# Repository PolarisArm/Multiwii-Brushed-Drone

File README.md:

# Multiwii-Brushed-Drone
Brushed Drone with Multiwii

# Orientation Code need to be changed as per MPU6050 Placement

# Vibration Issue mitigated by using low pass filter

# Dead band Added

# Multiwii 2.4 Software picture

#Transmitter Schematic

# Transmitter

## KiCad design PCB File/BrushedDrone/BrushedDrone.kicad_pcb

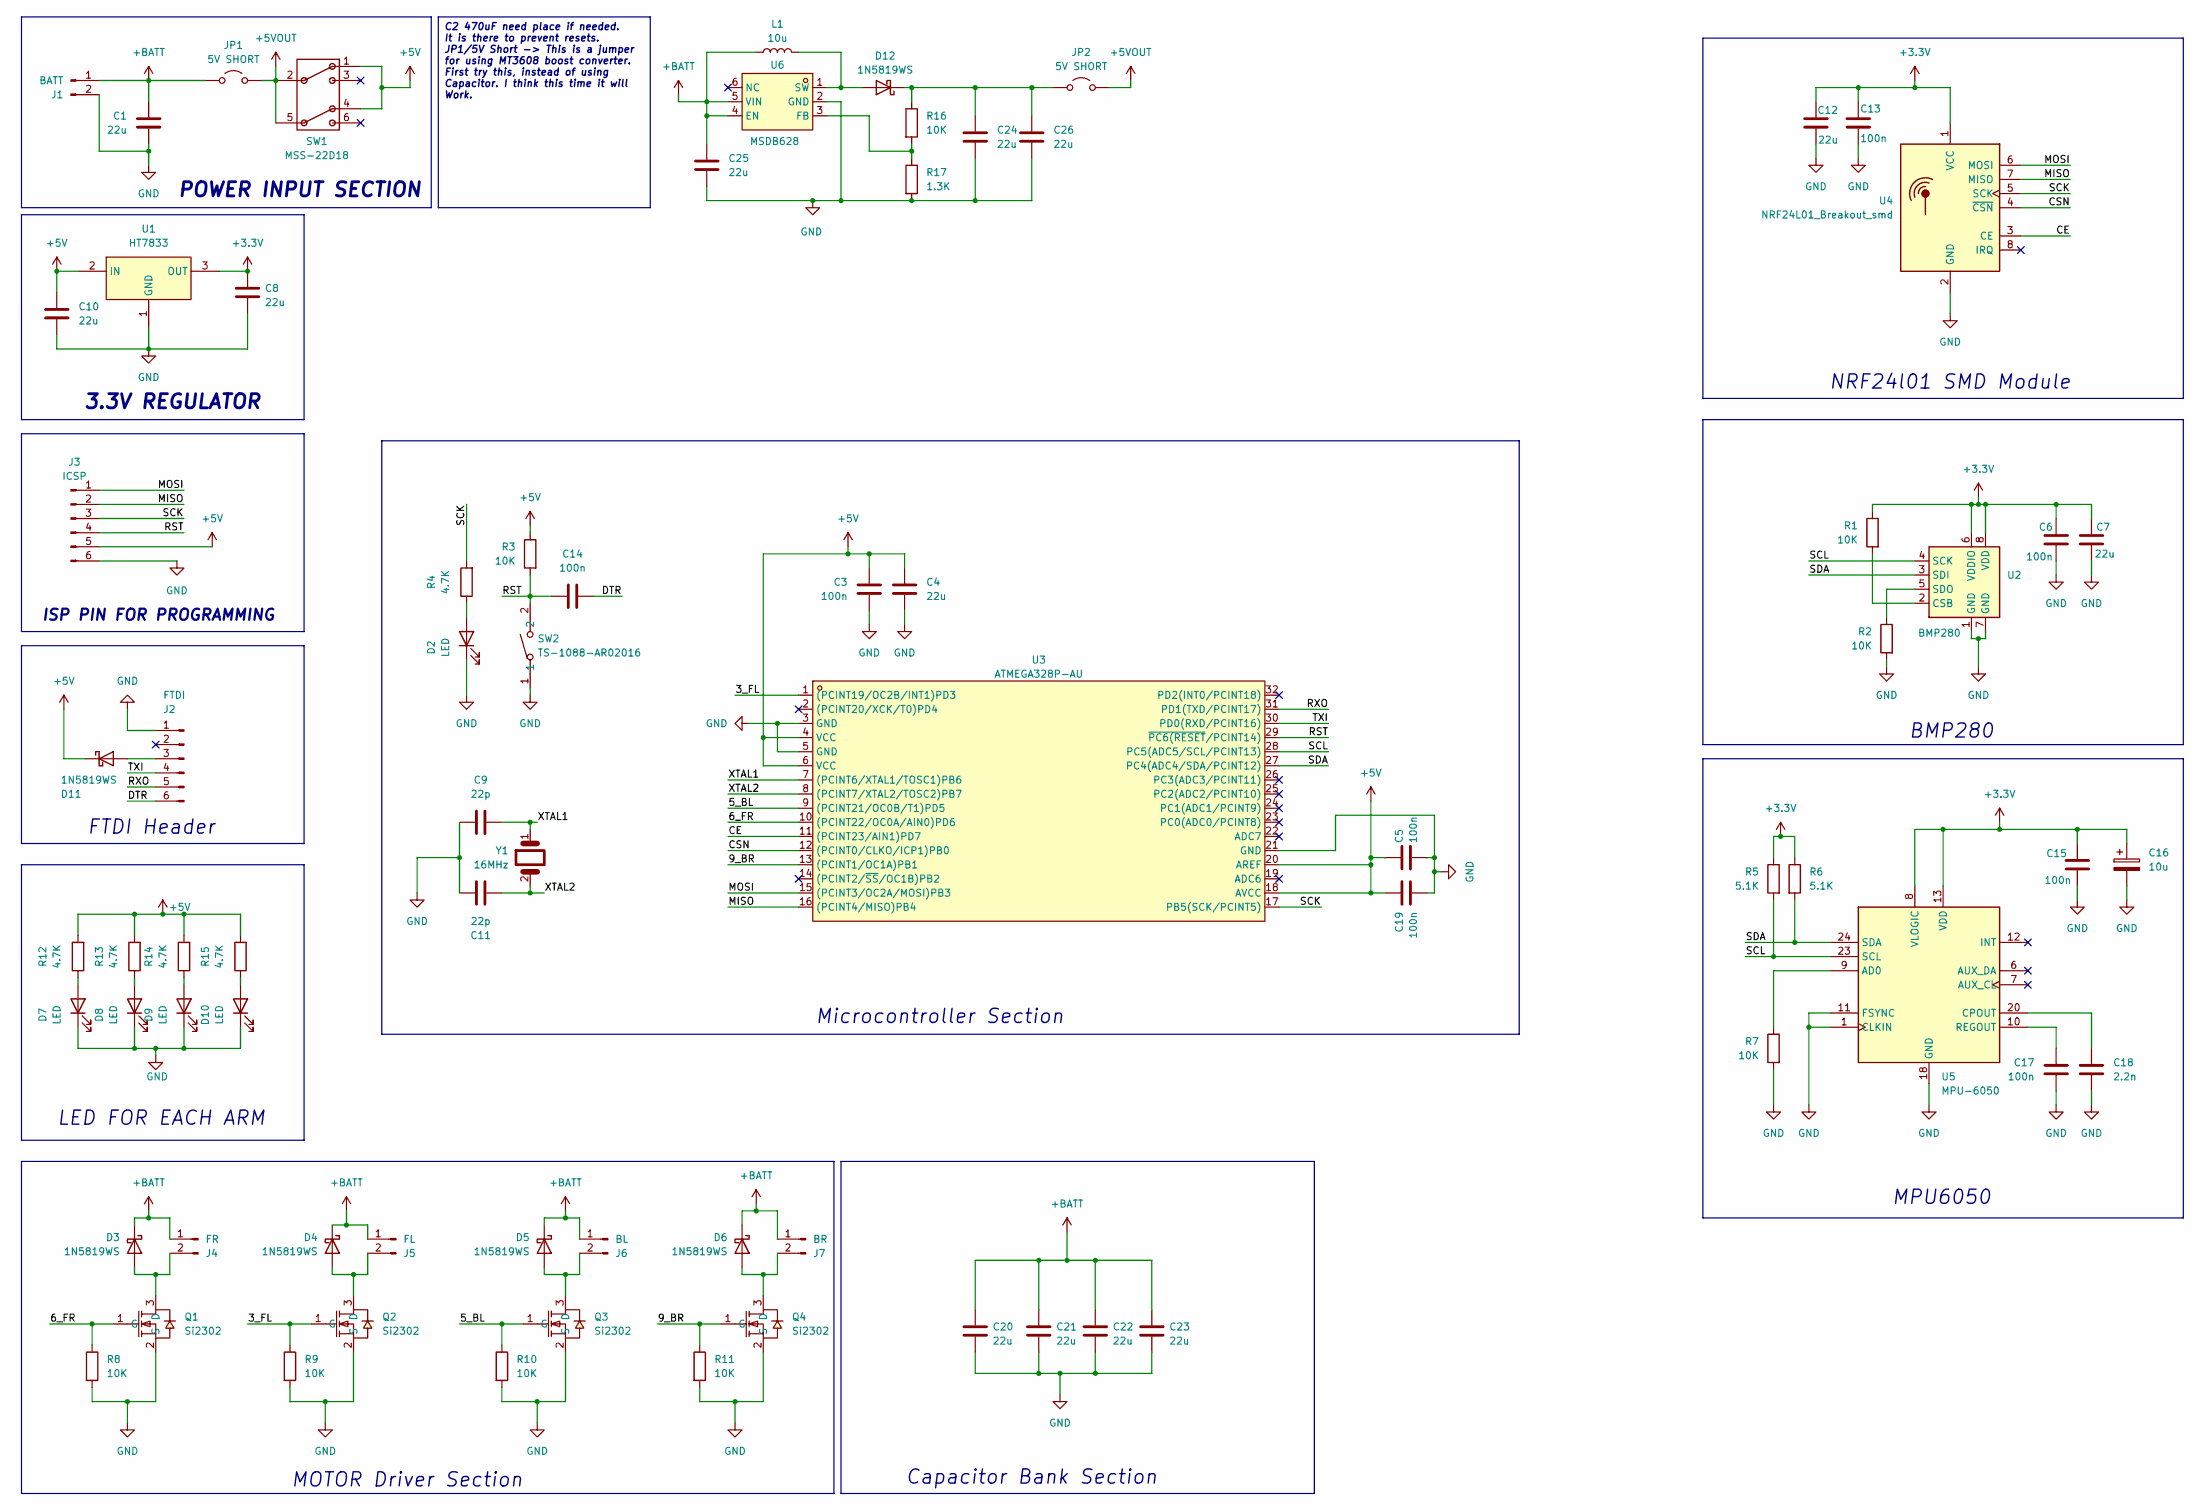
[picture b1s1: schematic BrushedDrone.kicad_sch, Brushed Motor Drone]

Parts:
C1, C4, C7, C8, C10, C12, C20, C21, C22, C23, C24, C25, C26: 22u; C_0805_2012Metric_Pad1.18x1.45mm_HandSolder
C3, C5, C6, C13, C14, C15, C17, C19: 100n; C_0805_2012Metric_Pad1.18x1.45mm_HandSolder
C9, C11: 22p; C_1206_3216Metric_Pad1.33x1.80mm_HandSolder
C16: 10u; CP_EIA-3528-12_Kemet-T_HandSolder
C18: 2.2n; C_0805_2012Metric_Pad1.18x1.45mm_HandSolder
D2, D7, D8, D9, D10: LED; LED_0805_2012Metric_Pad1.15x1.40mm_HandSolder
D3, D4, D5, D6, D11, D12: 1N5819WS; D_SOD-323_HandSoldering
J1: BATT; PinSocket_1x02_P2.54mm_Vertical
J2: FTDI; PinSocket_1x06_P2.54mm_Vertical
J3: ICSP; ICSP_PAD
J4: FR; PinSocket_1x02_P2.54mm_Vertical
J5: FL; PinSocket_1x02_P2.54mm_Vertical
J6: BL; PinSocket_1x02_P2.54mm_Vertical
J7: BR; PinSocket_1x02_P2.54mm_Vertical
JP1: 5V SHORT; TestPoint_2Pads_Pitch2.54mm_Drill0.8mm
JP2: 5V SHORT; SolderJumper-2_P1.3mm_Open_Pad1.0x1.5mm
L1: 10u; L_APV_ANR4020
Q1, Q2, Q3, Q4: Si2302; SOT-23_L2.9-W1.3-P1.90-LS2.4-BR; MPN Si2302CDS-T1-GE3; LCSC Part C10488
R1, R2, R3, R7, R8, R9, R10, R11: 10K; R_0805_2012Metric_Pad1.20x1.40mm_HandSolder
R4, R12, R13, R14, R15: 4.7K; R_0805_2012Metric_Pad1.20x1.40mm_HandSolder
R5, R6: 5.1K; R_0805_2012Metric_Pad1.20x1.40mm_HandSolder
R16: 10K; R_0603_1608Metric_Pad0.98x0.95mm_HandSolder
R17: 1.3K; R_0603_1608Metric_Pad0.98x0.95mm_HandSolder
SW1: MSS-22D18; MSS2D18
SW2: TS-1088-AR02016; SW-SMD_L3.9-W3.0-P4.45; MPN TS-1088-AR02016; LCSC Part C720477
U1: HT7833; SOT-89_L4.5-W2.5-P1.50-LS4.2-BR; MPN HT7833; LCSC Part C50936
U2: BMP280; Bosch_LGA-8_2x2.5mm_P0.65mm_ClockwisePinNumbering
U3: ATMEGA328P-AU; TQFP-32_L7.0-W7.0-P0.80-LS9.0-BL; MPN ATMEGA328P-AU; LCSC Part C14877
U4: NRF24L01_Breakout_smd; FootprintsKeyplus_nordic.prettyNRF24L01-Module-SMD
U5: MPU-6050; InvenSense_QFN-24_4x4mm_P0.5mm
U6: MSDB628; SOT-23-6_L2.9-W1.6-P0.95-LS2.8-BR; MPN MSDB628; LCSC Part C30197563
Y1: 16MHz; Crystal_HC49-4H_Vertical

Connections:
+3.3V: C6.1, C7.1, C8.1, C12.1, C13.1, C15.1, C16.1, R1.1, R5.1, R6.1, U1.3 (OUT), U2.6 (VDDIO), U2.8 (VDD), U4.1 (VCC), U5.8 (VLOGIC), U5.13 (VDD)
+5V: C3.1, C4.1, C5.1, C10.1, C19.1, D11.1 (K), J3.5, R3.1, R12.2, R13.2, R14.2, R15.2, SW1.1, SW1.4, U1.2 (IN), U3.4 (VCC), U3.6 (VCC), U3.18 (AVCC), U3.20 (AREF)
+5VOUT: JP1.2 (B), JP2.2 (B), SW1.2, SW1.5
+BATT: C1.1, C20.1, C21.1, C22.1, C23.1, C25.1, D3.1 (K), D4.1 (K), D5.1 (K), D6.1 (K), J1.1, J4.1, J5.1, J6.1, J7.1, JP1.1 (A), L1.1, U6.4 (EN), U6.5 (VIN)
/3_FL: Q2.1 (G), R9.1, U3.1 ((PCINT19/OC2B/INT1)PD3)
/5_BL: Q3.1 (G), R10.1, U3.9 ((PCINT21/OC0B/T1)PD5)
/6_FR: Q1.1 (G), R8.1, U3.10 ((PCINT22/OC0A/AIN0)PD6)
/9_BR: Q4.1 (G), R11.1, U3.13 ((PCINT1/OC1A)PB1)
/CE: U3.11 ((PCINT23/AIN1)PD7), U4.3 (CE)
/CSN: U3.12 ((PCINT0/CLKO/ICP1)PB0), U4.4 (~CSN)
/DTR: C14.2, J2.6
/MISO: J3.2, U3.16 ((PCINT4/MISO)PB4), U4.7 (MISO)
/MOSI: J3.1, U3.15 ((PCINT3/OC2A/MOSI)PB3), U4.6 (MOSI)
/RST: C14.1, J3.4, R3.2, SW2.2, U3.29 (~PC6(RESET/PCINT14))
/RXO: J2.5, U3.31 (PD1(TXD/PCINT17))
/SCK: J3.3, R4.2, U3.17 (PB5(SCK/PCINT5)), U4.5 (SCK)
/SCL: R5.2, U2.4 (SCK), U3.28 (PC5(ADC5/SCL/PCINT13)), U5.23 (SCL)
/SDA: R6.2, U2.3 (SDI), U3.27 (PC4(ADC4/SDA/PCINT12)), U5.24 (SDA)
/TXI: J2.4, U3.30 (PD0(RXD/PCINT16))
/XTAL1: C9.1, U3.7 ((PCINT6/XTAL1/TOSC1)PB6), Y1.1
/XTAL2: C11.1, U3.8 ((PCINT7/XTAL2/TOSC2)PB7), Y1.2
GND: C1.2, C3.2, C4.2, C5.2, C6.2, C7.2, C8.2, C9.2, C10.2, C11.2, C12.2, C13.2, C15.2, C16.2, C17.2, C18.2, C19.2, C20.2, C21.2, C22.2, C23.2, C24.2, C25.2, C26.2, D2.1 (K), D7.1 (K), D8.1 (K), D9.1 (K), D10.1 (K), J1.2, J2.1, J3.6, Q1.2 (S), Q2.2 (S), Q3.2 (S), Q4.2 (S), R2.2, R7.2, R8.2, R9.2, R10.2, R11.2, R17.2, SW2.1, U1.1 (GND), U2.1 (GND), U2.7 (GND), U3.3 (GND), U3.5 (GND), U3.21 (GND), U4.2 (GND), U5.1 (CLKIN), U5.11 (FSYNC), U5.18 (GND), U6.2 (GND)
unnamed: D2.2 (A), R4.1
unnamed: D3.2 (A), J4.2, Q1.3 (D)
unnamed: D4.2 (A), J5.2, Q2.3 (D)
unnamed: D5.2 (A), J6.2, Q3.3 (D)
unnamed: D6.2 (A), J7.2, Q4.3 (D)
unnamed: D7.2 (A), R12.1
unnamed: D8.2 (A), R13.1
unnamed: D9.2 (A), R14.1
unnamed: D10.2 (A), R15.1
unnamed: D11.2 (A), J2.3
unnamed: D12.2 (A), L1.2, U6.1 (SW)
unnamed: C24.1, C26.1, D12.1 (K), JP2.1 (A), R16.1
unnamed: R1.2, U2.2 (CSB)
unnamed: R2.1, U2.5 (SDO)
unnamed: R7.1, U5.9 (AD0)
unnamed: C18.1, U5.20 (CPOUT)
unnamed: C17.1, U5.10 (REGOUT)
unnamed: R16.2, R17.1, U6.3 (FB)

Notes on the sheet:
NRF24l01 SMD Module
BMP280
ISP PIN FOR PROGRAMMING
MOTOR Driver Section
MPU6050
LED FOR EACH ARM
POWER INPUT SECTION
Microcontroller Section
3.3V REGULATOR
Capacitor Bank Section
FTDI Header
C2 470uF need place if needed. It is there to prevent resets. JP1/5V Short -> This is a jumper for using MT3608 boost converter. First try this, instead of using Capacitor. I think this time it will Work.

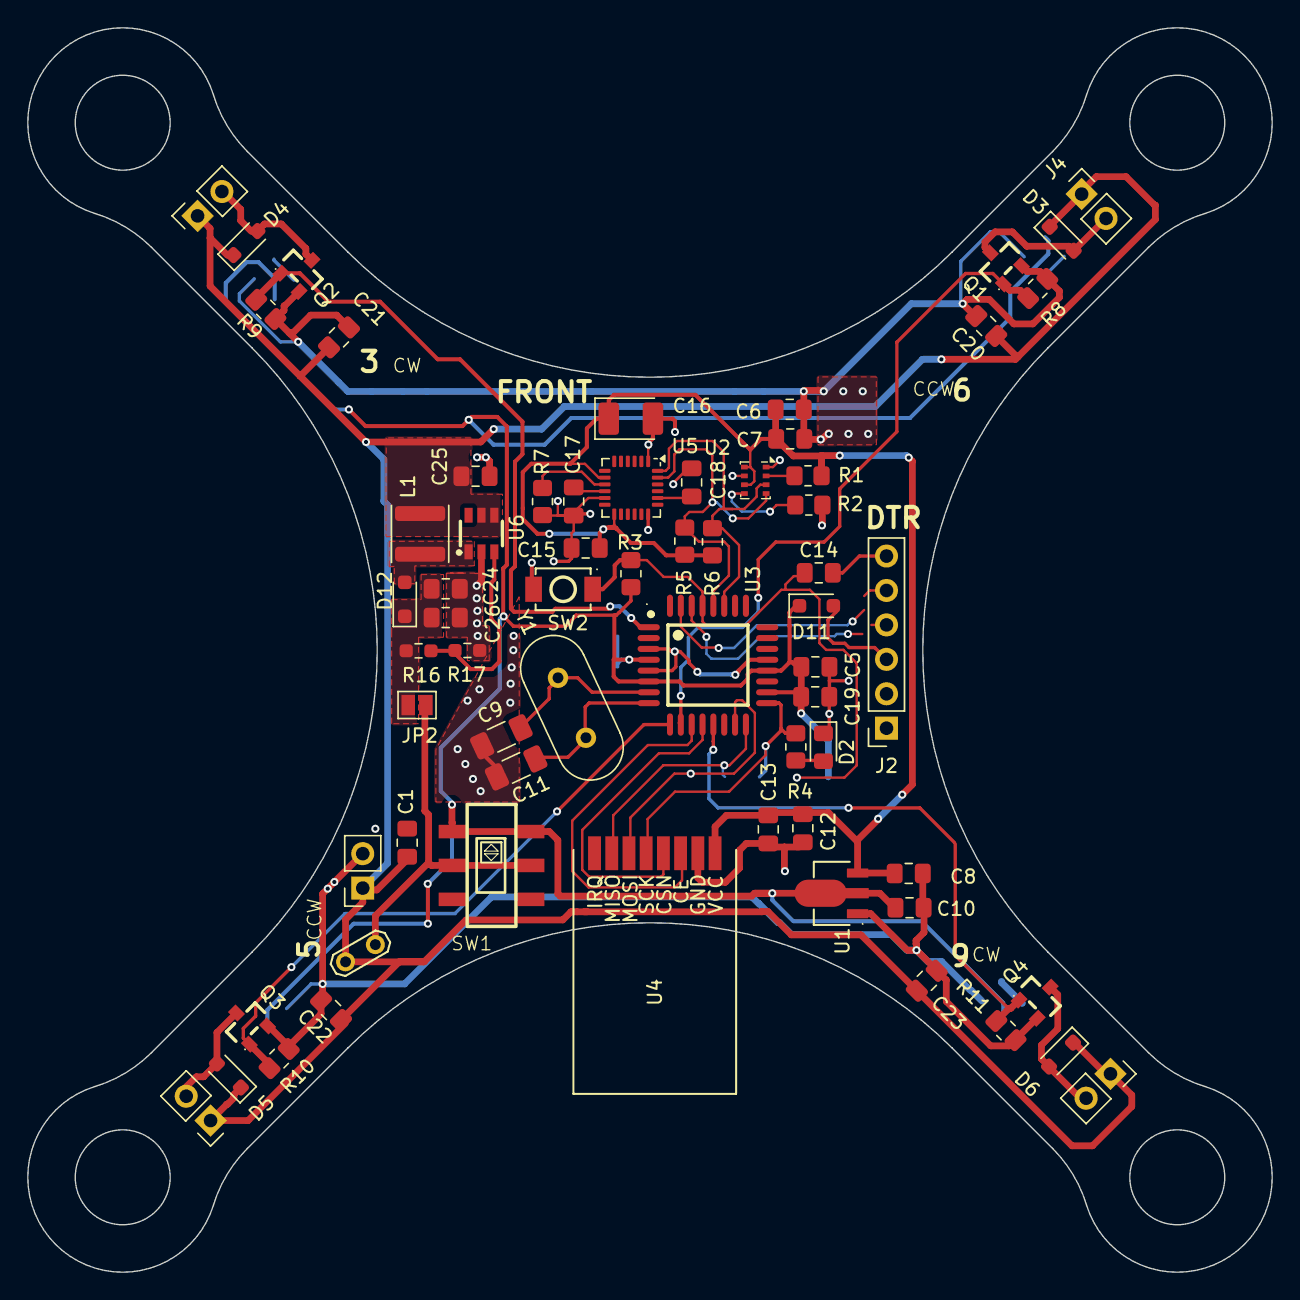
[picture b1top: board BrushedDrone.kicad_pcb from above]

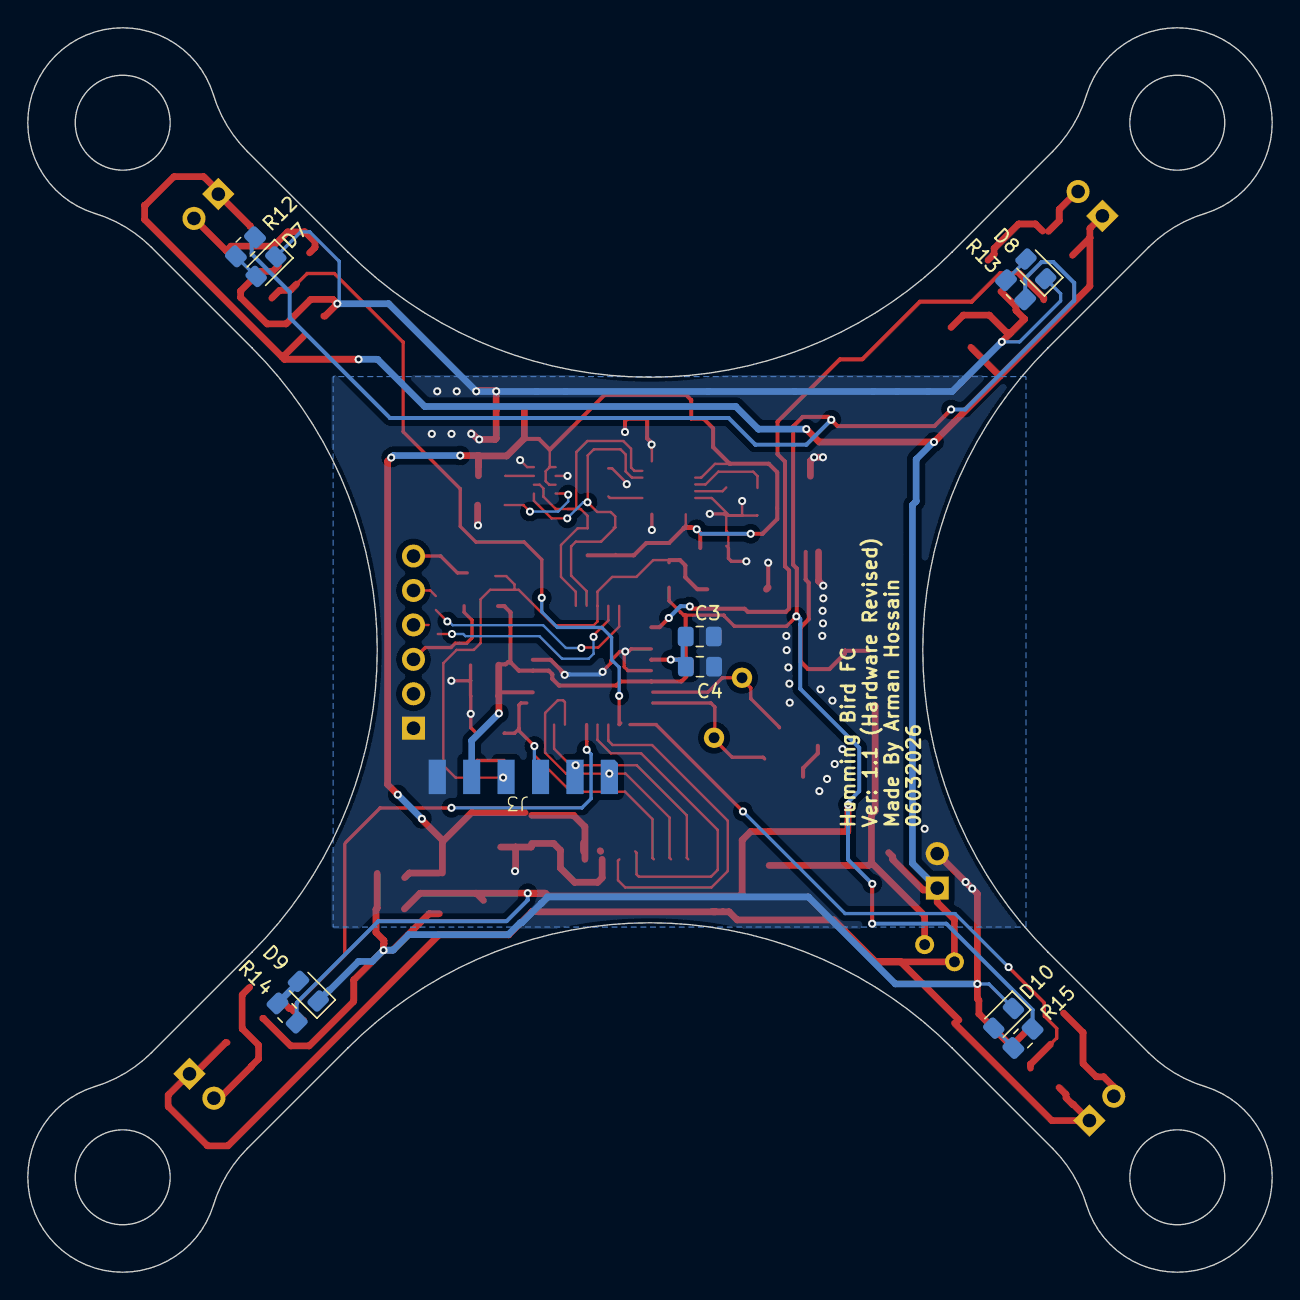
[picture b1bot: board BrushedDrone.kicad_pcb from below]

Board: 2 copper layers, 91.8 x 91.8 mm, 76 parts (11 on the bottom side), 40 nets.

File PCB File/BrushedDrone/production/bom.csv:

Designator,Footprint,Quantity,Value,LCSC Part #
"C1, C10, C12, C20, C21, C22, C23, C24, C25, C26, C4, C7, C8",0805,13,22u,
"C11, C9",1206,2,22p,
"C13, C14, C15, C17, C19, C3, C5, C6",0805,8,100n,
C16,CP_EIA-3528-12_Kemet-T_HandSolder,1,10u,
C18,0805,1,2.2n,
"D1, D3, D4, D5, D6",D_SOD-323_HandSoldering,5,1N5819WS,
"D10, D2, D7, D8, D9",0805,5,LED,
D11,D_SOD-323,1,1N5819WS,
J1,PinSocket_1x02_P2.54mm_Vertical,1,BATT,
J2,PinSocket_1x06_P2.54mm_Vertical,1,FTDI,
J3,ICSP_PAD,1,ICSP,
J4,PinSocket_1x02_P2.54mm_Vertical,1,FR,
J5,PinSocket_1x02_P2.54mm_Vertical,1,FL,
J6,PinSocket_1x02_P2.54mm_Vertical,1,BL,
J7,PinSocket_1x02_P2.54mm_Vertical,1,BR,
JP1,TestPoint_2Pads_Pitch2.54mm_Drill0.8mm,1,5V SHORT,
JP2,SolderJumper-2_P1.3mm_Open_Pad1.0x1.5mm,1,5V SHORT,
L1,L_APV_ANR4020,1,10u,
"Q1, Q2, Q3, Q4",SOT-23_L2.9-W1.3-P1.90-LS2.4-BR,4,Si2302,C10488
"R1, R10, R11, R2, R3, R7, R8, R9",0805,8,10K,
"R12, R13, R14, R15, R4",0805,5,4.7K,
R16,0603,1,10K,
R17,0603,1,1.3K,
"R5, R6",0805,2,5.1K,
SW1,MSS2D18,1,MSS-22D18,
SW2,SW-SMD_L3.9-W3.0-P4.45,1,TS-1088-AR02016,C720477
U1,SOT-89_L4.5-W2.5-P1.50-LS4.2-BR,1,HT7833,C50936
U2,Bosch_LGA-8_2x2.5mm_P0.65mm_ClockwisePinNumbering,1,BMP280,
U3,TQFP-32_L7.0-W7.0-P0.80-LS9.0-BL,1,ATMEGA328P-AU,C14877
U4,FootprintsKeyplus_nordic.prettyNRF24L01-Module-SMD,1,NRF24L01_Breakout_smd,
U5,InvenSense_QFN-24_4x4mm_P0.5mm,1,MPU-6050,
U6,SOT-23-6_L2.9-W1.6-P0.95-LS2.8-BR,1,MSDB628,C30197563
Y1,Crystal_HC49-4H_Vertical,1,16MHz,
